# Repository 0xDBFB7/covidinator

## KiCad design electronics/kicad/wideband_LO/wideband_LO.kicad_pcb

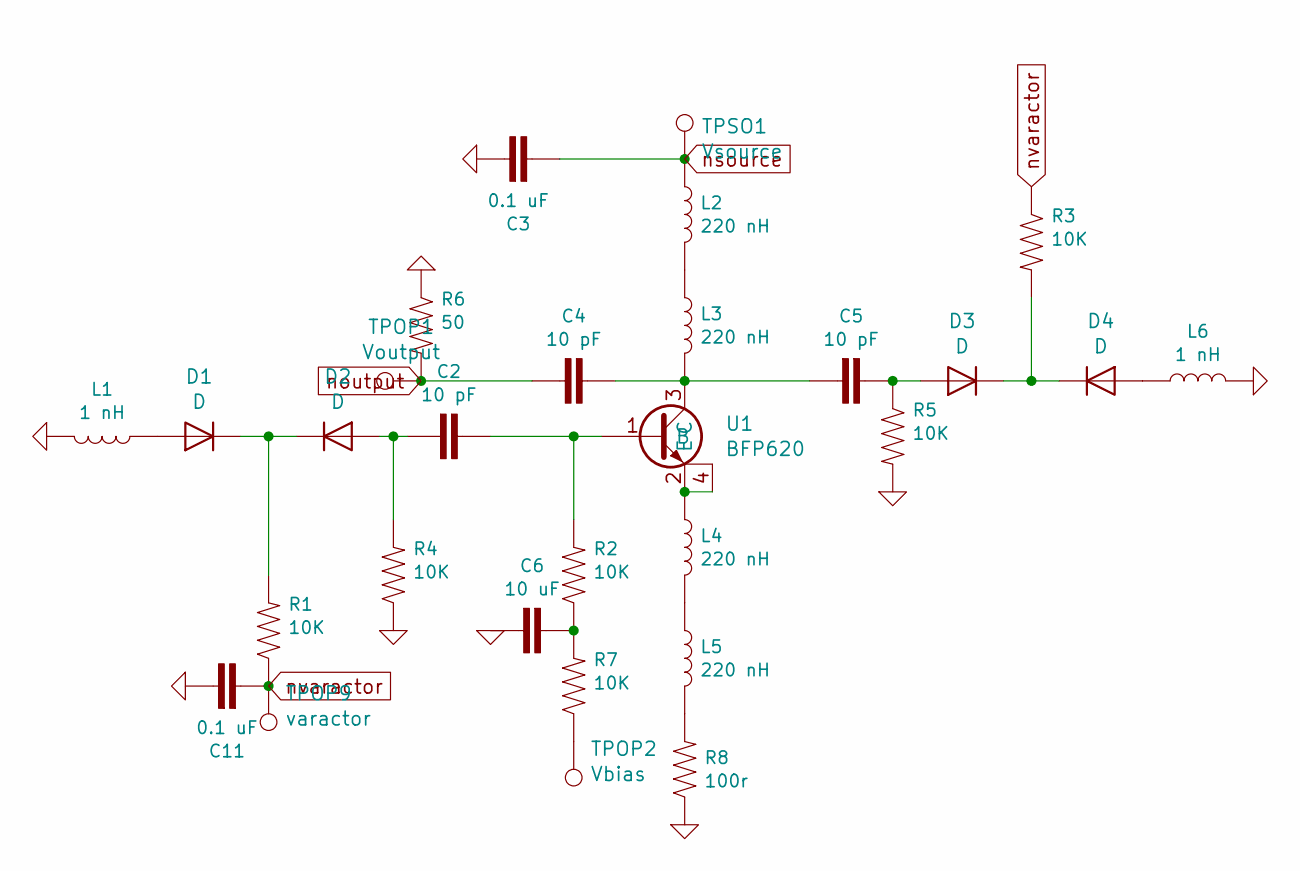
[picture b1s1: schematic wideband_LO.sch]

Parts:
C2, C4, C5: 10 pF; C_0402_1005Metric
C3, C11: 0.1 uF; 0603
C6: 10 uF; 0603
D1, D2, D3, D4: D; D_SOD-523
L1, L6: 1 nH; R_0402_1005Metric
L2, L3, L4, L5: 220 nH; R_0402_1005Metric
R1, R2, R3, R4, R5, R7: 10K; R_0402_1005Metric
R6: 50; R_0402_1005Metric
R8: 100r; 0603
TPOP1: Voutput; TestPoint_Pad_1.5x1.5mm
TPOP2: Vbias; TestPoint_Pad_1.5x1.5mm
TPOP9: varactor; TestPoint_Pad_1.5x1.5mm
TPSO1: Vsource; TestPoint_Pad_2.0x2.0mm
U1: BFP620; SOT-343_SC-70-4

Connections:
GND: C3.1, C6.2, C11.1, L1.2, L6.2, R4.1, R5.2, R6.1, R8.1
unnamed: C2.1, R2.2, U1.1 (B)
unnamed: C2.2, D2.2 (A), R4.2
unnamed: C4.1, C5.2, L3.2, U1.3 (C)
unnamed: C5.1, D3.2 (A), R5.1
unnamed: C6.1, R2.1, R7.2
unnamed: D1.1 (K), D2.1 (K), R1.2
unnamed: D1.2 (A), L1.1
unnamed: D3.1 (K), D4.1 (K), R3.2
unnamed: D4.2 (A), L6.1
unnamed: L2.2, L3.1
unnamed: L4.1, U1.2 (E), U1.4
unnamed: L4.2, L5.1
unnamed: L5.2, R8.2
unnamed: R7.1, TPOP2.1
noutput: C4.2, R6.2, TPOP1.1
nsource: C3.2, L2.1, TPSO1.1
nvaractor: C11.2, R1.1, R3.1, TPOP9.1

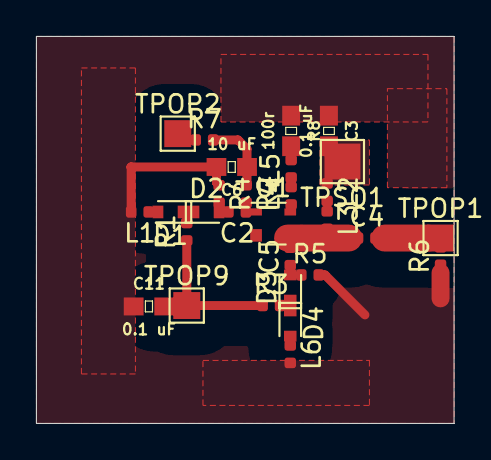
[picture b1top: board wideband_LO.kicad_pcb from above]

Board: 2 copper layers, 23.2 x 21.5 mm, 29 parts (0 on the bottom side), 18 nets.

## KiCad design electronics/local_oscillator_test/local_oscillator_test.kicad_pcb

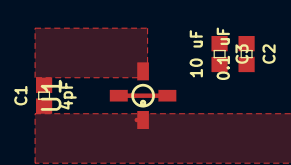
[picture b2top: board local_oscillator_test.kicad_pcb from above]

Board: 2 copper layers, 4 parts (0 on the bottom side), 4 nets.

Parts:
C1: 4pF; 0402
C2: 0.1 uF; 0402
C3: 10 uF; 0402
U1: CE3520K3; 4-Micro-X

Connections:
/GATE: C1.1, U1.4
/OSC1: C1.2, C2.1, C3.1, U1.2
GND: C2.2, C3.2
unnamed: U1.1, U1.3
